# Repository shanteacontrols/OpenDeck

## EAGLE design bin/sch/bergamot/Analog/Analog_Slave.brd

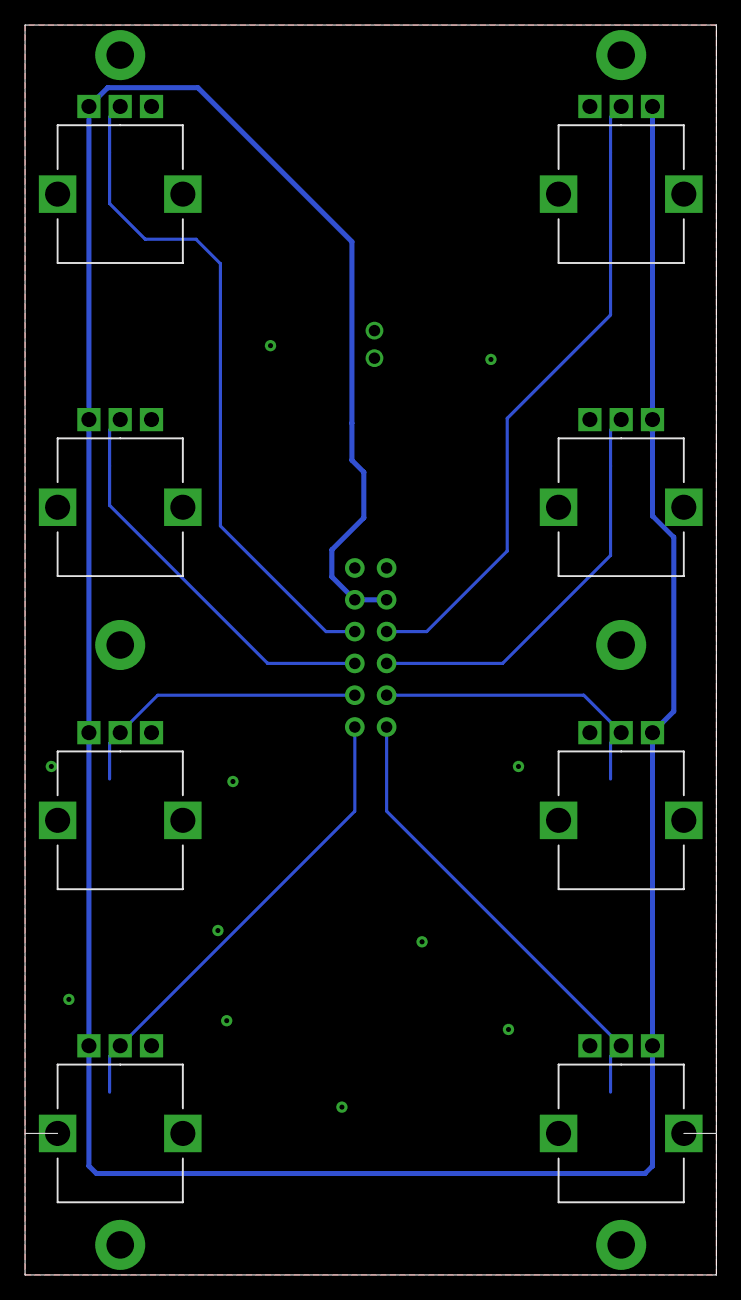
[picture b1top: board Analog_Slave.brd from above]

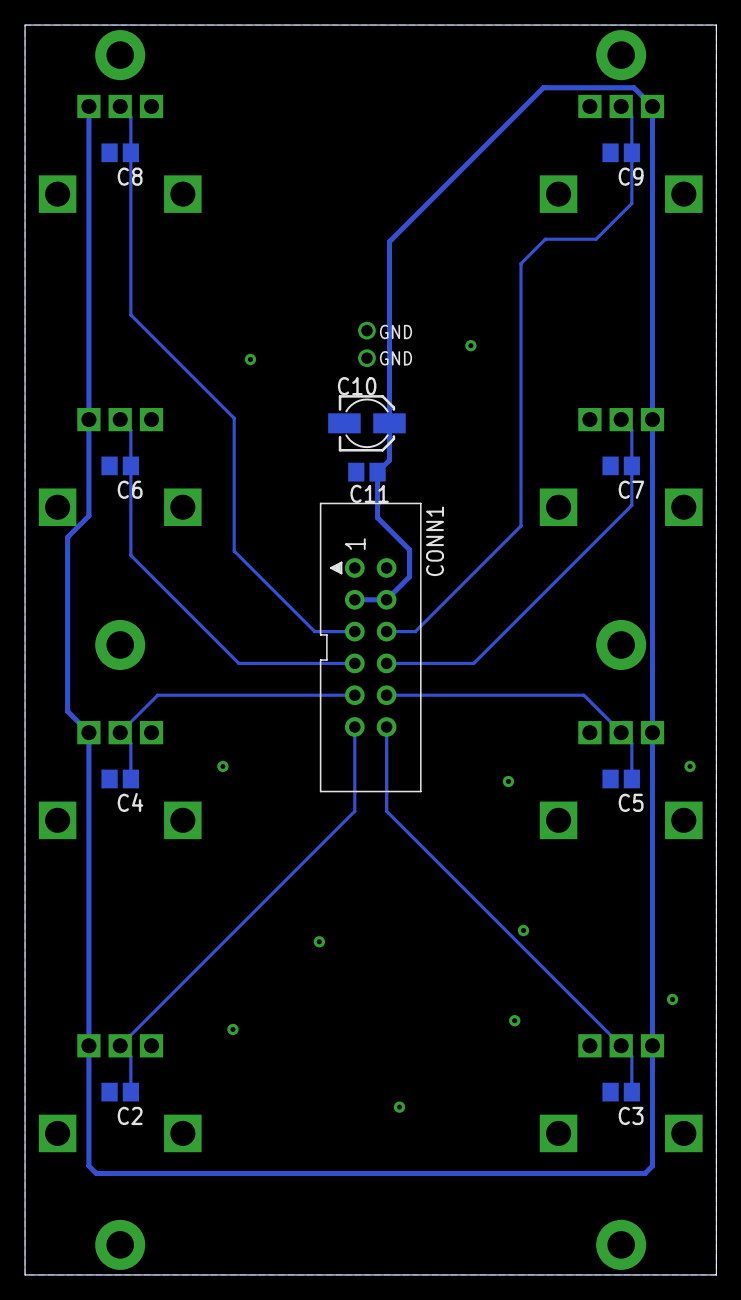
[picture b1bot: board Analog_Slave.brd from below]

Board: 2 copper layers, 55.2 x 99.8 mm, 19 parts (11 on the bottom side), 10 nets.

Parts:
C2, C3, C4, C5, C6, C7, C8, C9, C11: 100n; C0805
C10: 10u; 153CLV-0405
CONN1: PINHD-2X06-IDC-2.54-V; IDC-12P-2.54
R3, R4, R5, R6, R7, R8, R9, R10: 10k; PTV09A-4025F-B103

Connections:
+3V3: C10.+, C11.1, CONN1.3, CONN1.4, R3.1, R4.3, R5.1, R6.3, R7.1, R8.3, R9.1, R10.3
AS_1: C2.1, CONN1.11, R3.2
AS_2: C3.1, CONN1.12, R4.2
AS_3: C4.1, CONN1.9, R5.2
AS_4: C5.1, CONN1.10, R6.2
AS_5: C6.1, CONN1.7, R7.2
AS_6: C7.1, CONN1.8, R8.2
AS_7: C8.1, CONN1.5, R9.2
AS_8: C9.1, CONN1.6, R10.2
GND: C2.2, C3.2, C4.2, C5.2, C6.2, C7.2, C8.2, C9.2, C10.-, C11.2, CONN1.1, CONN1.2, R3.3, R3.S1, R3.S2, R4.1, R4.S1, R4.S2, R5.3, R5.S1, R5.S2, R6.1, R6.S1, R6.S2, R7.3, R7.S1, R7.S2, R8.1, R8.S1, R8.S2, R9.3, R9.S1, R9.S2, R10.1, R10.S1, R10.S2

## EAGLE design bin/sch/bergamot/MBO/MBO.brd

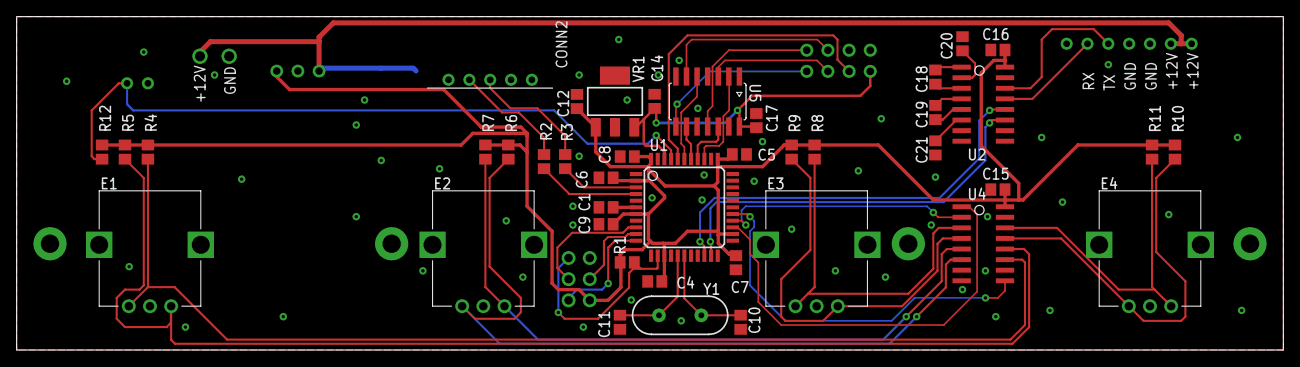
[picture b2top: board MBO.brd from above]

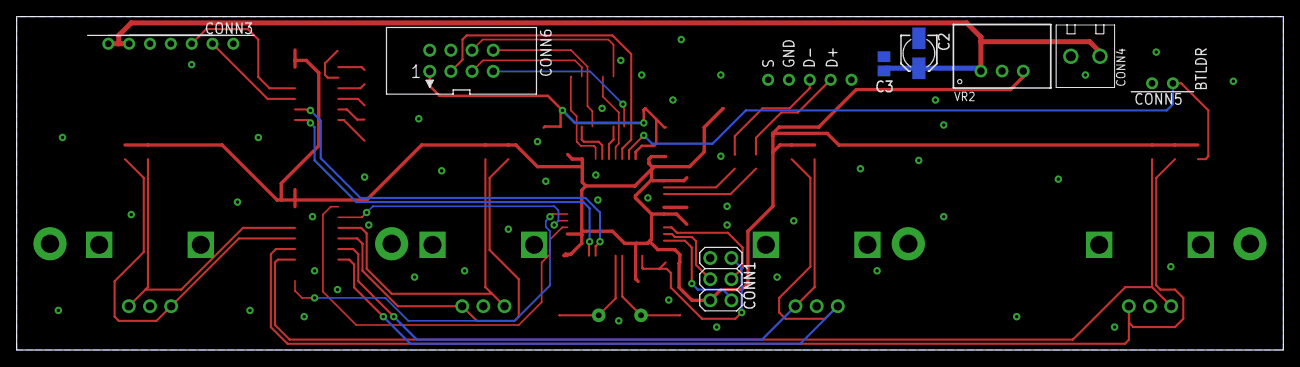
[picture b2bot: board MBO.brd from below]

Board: 2 copper layers, 152.0 x 40.0 mm, 49 parts (8 on the bottom side), 46 nets.

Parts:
C1: 1u; C0805
C2: 10n; 153CLV-0405
C3, C4, C5, C6, C7, C8, C9, C15, C16, C17, C18, C19, C20, C21: 100n; C0805
C10, C11: 22p; C0805
C12, C14: 4.7u; C0805
CONN1: PINHD-2X03-TH-2.54MM-V; 2X03-2.54-V
CONN2: PINHD-1X05-JST-XH-H; JST-XH-05P-H
CONN3: PINHD-1X07-JST-H; JST-XH-07P-H
CONN4: PINHD-1X02-MOLEX-39357-0002; MOLEX-39357-0002
CONN5: PINHD-1X02-JST-XH-H; JST-XH-02P-H
CONN6: PINHD-2X04-IDC-2.54-V; IDC-08P-2.54
E1, E2, E3, E4: ALPS-EC12E24404AX; EC12E-1
R1, R4, R5, R6, R7, R8, R9, R10, R11, R12: 10k; R0805
R2, R3: 22; R0805
U1: ATMEGA-32U4TQFP; TQFP-44
U2: MAX3232; SO16
U4: 74HC165; SO16
U5: 74AHC125; SOIC14
VR1: MCP1825; SOT223
VR2: TSR-1-2450
Y1: 16MHz; HC49US

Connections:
+3V3: C14.1, C17.1, CONN6.1, U1.42, U5.14, VR1.3
+5V: C4.1, C5.1, C6.1, C7.1, C8.1, C9.1, C12.1, C15.2, C16.2, CONN1.2, R1.2, R4.2, R5.2, R6.2, R7.2, R8.2, R9.2, R10.2, R11.2, R12.2, U1.2, U1.7, U1.14, U1.24, U1.34, U1.44, U2.16, U4.16, VR1.1, VR2.3
+12V: C2.+, C3.1, CONN3.6, CONN3.7, CONN4.P$1, VR2.1
BTLDR_BUTTON: CONN5.2, R12.1, U1.41
C1+: C18.1, U2.1
C1-: C18.2, U2.3
C2+: C19.1, U2.4
C2-: C19.2, U2.5
D+: R2.1, U1.4
D+R: CONN2.2, R2.2
D-: R3.1, U1.3
D-R: CONN2.3, R3.2
DISPLAY_RX_5V: U1.20, U2.12
DISPLAY_RX_RS: CONN3.2, U2.13
DISPLAY_TX_5V: U1.21, U2.11
DISPLAY_TX_RS: CONN3.3, U2.14
E1A: E1.A, R4.1, U4.11
E1B: E1.B, R5.1, U4.12
E2A: E2.A, R6.1, U4.6
E2B: E2.B, R7.1, U4.5
E3A: E3.A, R8.1, U4.3
E3B: E3.B, R9.1, U4.4
E4A: E4.A, R10.1, U4.13
E4B: E4.B, R11.1, U4.14
GND: C1.2, C2.-, C3.2, C4.2, C5.2, C6.2, C7.2, C8.2, C9.2, C10.1, C11.1, C12.2, C14.2, C15.1, C16.1, C17.2, C20.2, C21.2, CONN1.6, CONN2.4, CONN2.5, CONN3.4, CONN3.5, CONN4.P$2, CONN5.1, CONN6.2, CONN6.4, E1.C, E1.S1, E1.S2, E2.C, E2.S1, E2.S2, E3.C, E3.S1, E3.S2, E4.C, E4.S1, E4.S2, U1.5, U1.15, U1.23, U1.35, U1.43, U2.10, U2.15, U4.8, U4.15, U5.1, U5.4, U5.7, U5.10, U5.13, VR1.2, VR1.4, VR2.2
MISO: CONN1.1, U1.11
MOSI: CONN1.4, U1.10
MUX_COMMON_1: CONN6.3, U1.40
MUX_S0_3V3: CONN6.8, U5.11
MUX_S0_5V: U1.37, U5.12
MUX_S1_3V3: CONN6.7, U5.8
MUX_S1_5V: U1.38, U5.9
MUX_S2_3V3: CONN6.5, U5.3
MUX_S2_5V: U1.36, U5.2
MUX_S3_3V3: CONN6.6, U5.6
MUX_S3_5V: U1.39, U5.5
unnamed: C1.1, U1.6
RESET: CONN1.5, R1.1, U1.13
SCK: CONN1.3, U1.9
SR_DIN_CLOCK: U1.26, U4.2
SR_DIN_DATA: U1.27, U4.9
SR_DIN_LATCH: U1.25, U4.1
V+: C20.1, U2.2
V-: C21.1, U2.6
XTAL1: C10.2, U1.17, Y1.1
XTAL2: C11.2, U1.16, Y1.2

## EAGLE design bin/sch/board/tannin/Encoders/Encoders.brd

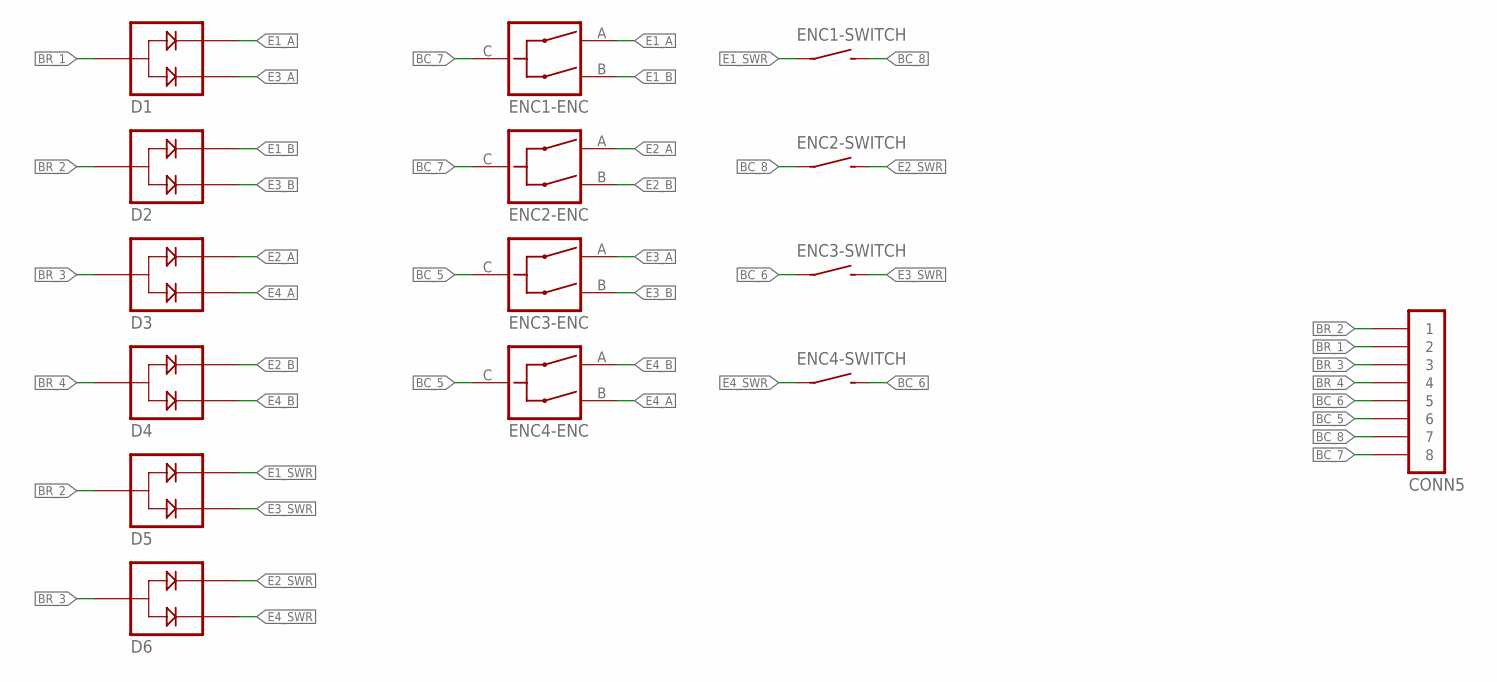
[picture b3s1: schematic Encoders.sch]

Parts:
CONN5: PINHD-1X08-FFC-1MM; MOLEX-52793-0870
D1, D2, D3, D4, D5, D6: BAW56; SOT23
ENC1, ENC2, ENC3, ENC4: BOURNS-PEC12R-4XXXF-SXXXX; PEC12R-42XXF-S0024

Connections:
BC_5: CONN5.6, ENC3.C, ENC4.C
BC_6: CONN5.5, ENC3.SW1 (1), ENC4.SW2 (2)
BC_7: CONN5.8, ENC1.C, ENC2.C
BC_8: CONN5.7, ENC1.SW2 (2), ENC2.SW1 (1)
BR_1: CONN5.2, D1.3
BR_2: CONN5.1, D2.3, D5.3
BR_3: CONN5.3, D3.3, D6.3
BR_4: CONN5.4, D4.3
E1_A: D1.2, ENC1.A
E1_B: D2.2, ENC1.B
E1_SWR: D5.2, ENC1.SW1 (1)
E2_A: D3.2, ENC2.A
E2_B: D4.2, ENC2.B
E2_SWR: D6.2, ENC2.SW2 (2)
E3_A: D1.1, ENC3.A
E3_B: D2.1, ENC3.B
E3_SWR: D5.1, ENC3.SW2 (2)
E4_A: D3.1, ENC4.B
E4_B: D4.1, ENC4.A
E4_SWR: D6.1, ENC4.SW1 (1)

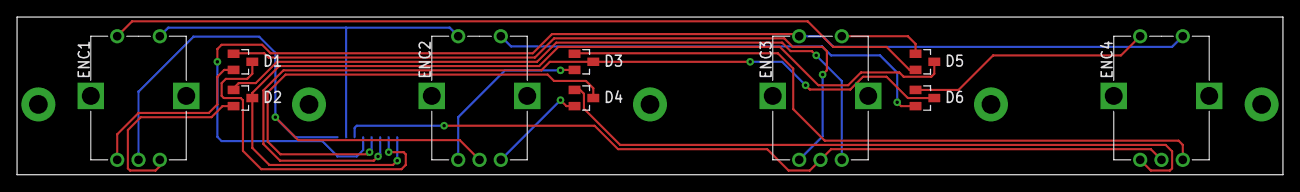
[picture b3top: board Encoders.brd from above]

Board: 2 copper layers, 148.5 x 18.5 mm, 11 parts (1 on the bottom side), 20 nets.

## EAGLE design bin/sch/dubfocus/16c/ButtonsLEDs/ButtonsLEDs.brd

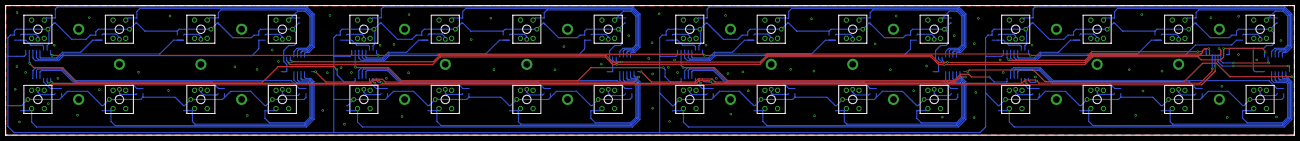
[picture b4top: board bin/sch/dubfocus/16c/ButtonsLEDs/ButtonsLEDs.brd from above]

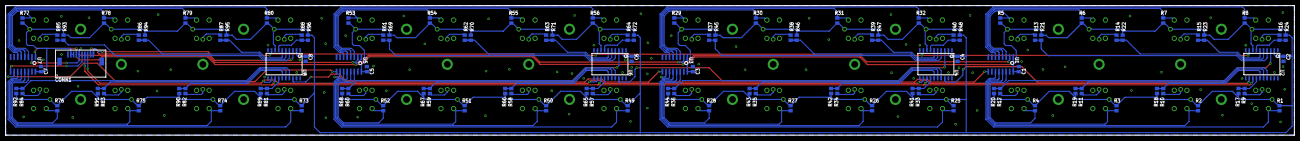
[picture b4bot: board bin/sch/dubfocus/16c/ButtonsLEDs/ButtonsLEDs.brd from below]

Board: 2 copper layers, 458.7 x 46.1 mm, 145 parts (113 on the bottom side), 111 nets.

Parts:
C1, C2, C3, C4, C5, C6, C7, C8: 100n; C0805
CONN1: PINHD-1X10-FFC-1MM-Z; MOLEX-52271-1079
R1, R2, R3, R4, R5, R6, R7, R8, R17, R18, R19, R20, R21, R22, R23, R24, R25, R26, R27, R28, R29, R30, R31, R32, R41, R42, R43, R44, R45, R46, R47, R48, R49, R50, R51, R52, R53, R54, R55, R56, R65, R66, R67, R68, R69, R70, R71, R72, R73, R74, R75, R76, R77, R78, R79, R80, R89, R90, R91, R92, R93, R94, R95, R96: 4k7; R0805
R9, R10, R11, R12, R13, R14, R15, R16, R33, R34, R35, R36, R37, R38, R39, R40, R57, R58, R59, R60, R61, R62, R63, R64, R81, R82, R83, R84, R85, R86, R87, R88: 750; R0805
SW1, SW2, SW3, SW4, SW5, SW6, SW7, SW8, SW9, SW10, SW11, SW12, SW13, SW14, SW15, SW16, SW17, SW18, SW19, SW20, SW21, SW22, SW23, SW24, SW25, SW26, SW27, SW28, SW29, SW30, SW31, SW32: OMRON-B3W-9
U1, U3, U5, U7: 74HC165; SO16
U2, U4, U6, U8: TPIC6B595; SOIC20

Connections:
+3V3: C1.1, C2.1, C3.1, C4.1, C5.1, C6.1, C7.1, C8.1, CONN1.2, CONN1.3, R1.2, R2.2, R3.2, R4.2, R5.2, R6.2, R7.2, R8.2, R17.2, R18.2, R19.2, R20.2, R21.2, R22.2, R23.2, R24.2, R25.2, R26.2, R27.2, R28.2, R29.2, R30.2, R31.2, R32.2, R41.2, R42.2, R43.2, R44.2, R45.2, R46.2, R47.2, R48.2, R49.2, R50.2, R51.2, R52.2, R53.2, R54.2, R55.2, R56.2, R65.2, R66.2, R67.2, R68.2, R69.2, R70.2, R71.2, R72.2, R73.2, R74.2, R75.2, R76.2, R77.2, R78.2, R79.2, R80.2, R89.2, R90.2, R91.2, R92.2, R93.2, R94.2, R95.2, R96.2, SW1.6-A, SW2.6-A, SW3.6-A, SW4.6-A, SW5.6-A, SW6.6-A, SW7.6-A, SW8.6-A, SW9.6-A, SW10.6-A, SW11.6-A, SW12.6-A, SW13.6-A, SW14.6-A, SW15.6-A, SW16.6-A, SW17.6-A, SW18.6-A, SW19.6-A, SW20.6-A, SW21.6-A, SW22.6-A, SW23.6-A, SW24.6-A, SW25.6-A, SW26.6-A, SW27.6-A, SW28.6-A, SW29.6-A, SW30.6-A, SW31.6-A, SW32.6-A, U1.16, U2.2, U2.8, U3.16, U4.2, U4.8, U5.16, U6.2, U6.8, U7.16, U8.2, U8.8
BUTTON1: R1.1, SW1.1, U1.11
BUTTON2: R2.1, SW2.1, U1.12
BUTTON3: R3.1, SW3.1, U1.13
BUTTON4: R4.1, SW4.1, U1.14
BUTTON5: R5.1, SW5.1, U1.3
BUTTON6: R6.1, SW6.1, U1.4
BUTTON7: R7.1, SW7.1, U1.5
BUTTON8: R8.1, SW8.1, U1.6
BUTTON9: R25.1, SW9.1, U3.11
BUTTON10: R26.1, SW10.1, U3.12
BUTTON11: R27.1, SW11.1, U3.13
BUTTON12: R28.1, SW12.1, U3.14
BUTTON13: R29.1, SW13.1, U3.3
BUTTON14: R30.1, SW14.1, U3.4
BUTTON15: R31.1, SW15.1, U3.5
BUTTON16: R32.1, SW16.1, U3.6
BUTTON17: R49.1, SW17.1, U5.11
BUTTON18: R50.1, SW18.1, U5.12
BUTTON19: R51.1, SW19.1, U5.13
BUTTON20: R52.1, SW20.1, U5.14
BUTTON21: R53.1, SW21.1, U5.3
BUTTON22: R54.1, SW22.1, U5.4
BUTTON23: R55.1, SW23.1, U5.5
BUTTON24: R56.1, SW24.1, U5.6
BUTTON25: R73.1, SW25.1, U7.11
BUTTON26: R74.1, SW26.1, U7.12
BUTTON27: R75.1, SW27.1, U7.13
BUTTON28: R76.1, SW28.1, U7.14
BUTTON29: R77.1, SW29.1, U7.3
BUTTON30: R78.1, SW30.1, U7.4
BUTTON31: R79.1, SW31.1, U7.5
BUTTON32: R80.1, SW32.1, U7.6
GND: C1.2, C2.2, C3.2, C4.2, C5.2, C6.2, C7.2, C8.2, CONN1.1, SW1.3, SW2.3, SW3.3, SW4.3, SW5.3, SW6.3, SW7.3, SW8.3, SW9.3, SW10.3, SW11.3, SW12.3, SW13.3, SW14.3, SW15.3, SW16.3, SW17.3, SW18.3, SW19.3, SW20.3, SW21.3, SW22.3, SW23.3, SW24.3, SW25.3, SW26.3, SW27.3, SW28.3, SW29.3, SW30.3, SW31.3, SW32.3, U1.8, U1.15, U2.10, U2.11, U2.19, U3.8, U3.15, U4.10, U4.11, U4.19, U5.8, U5.15, U6.10, U6.11, U6.19, U7.8, U7.15, U8.10, U8.11, U8.19
LED1: R9.2, R17.1, U2.14
LED1_R: R9.1, SW1.6-C
LED2: R10.2, R18.1, U2.15
LED2_R: R10.1, SW2.6-C
LED3: R11.2, R19.1, U2.16
LED3_R: R11.1, SW3.6-C
LED4: R12.2, R20.1, U2.17
LED4_R: R12.1, SW4.6-C
LED5: R13.2, R21.1, U2.4
LED5_R: R13.1, SW5.6-C
LED6: R14.2, R22.1, U2.5
LED6_R: R14.1, SW6.6-C
LED7: R15.2, R23.1, U2.6
LED7_R: R15.1, SW7.6-C
LED8: R16.2, R24.1, U2.7
LED8_R: R16.1, SW8.6-C
LED9: R33.2, R41.1, U4.14
LED9_R: R33.1, SW9.6-C
LED10: R34.2, R42.1, U4.15
LED10_R: R34.1, SW10.6-C
LED11: R35.2, R43.1, U4.16
LED11_R: R35.1, SW11.6-C
LED12: R36.2, R44.1, U4.17
LED12_R: R36.1, SW12.6-C
LED13: R37.2, R45.1, U4.4
LED13_R: R37.1, SW13.6-C
LED14: R38.2, R46.1, U4.5
LED14_R: R38.1, SW14.6-C
LED15: R39.2, R47.1, U4.6
LED15_R: R39.1, SW15.6-C
LED16: R40.2, R48.1, U4.7
LED16_R: R40.1, SW16.6-C
LED17: R57.2, R65.1, U6.14
LED17_R: R57.1, SW17.6-C
LED18: R58.2, R66.1, U6.15
LED18_R: R58.1, SW18.6-C
LED19: R59.2, R67.1, U6.16
LED19_R: R59.1, SW19.6-C
LED20: R60.2, R68.1, U6.17
LED20_R: R60.1, SW20.6-C
LED21: R61.2, R69.1, U6.4
LED21_R: R61.1, SW21.6-C
LED22: R62.2, R70.1, U6.5
LED22_R: R62.1, SW22.6-C
LED23: R63.2, R71.1, U6.6
LED23_R: R63.1, SW23.6-C
LED24: R64.2, R72.1, U6.7
LED24_R: R64.1, SW24.6-C
LED25: R81.2, R89.1, U8.14
LED25_R: R81.1, SW25.6-C
LED26: R82.2, R90.1, U8.15
LED26_R: R82.1, SW26.6-C
LED27: R83.2, R91.1, U8.16
LED27_R: R83.1, SW27.6-C
LED28: R84.2, R92.1, U8.17
LED28_R: R84.1, SW28.6-C
LED29: R85.2, R93.1, U8.4
LED29_R: R85.1, SW29.6-C
LED30: R86.2, R94.1, U8.5
LED30_R: R86.1, SW30.6-C
LED31: R87.2, R95.1, U8.6
LED31_R: R87.1, SW31.6-C
LED32: R88.2, R96.1, U8.7
LED32_R: R88.1, SW32.6-C
SR_IN_CLOCK: CONN1.5, U1.2, U3.2, U5.2, U7.2
SR_IN_DAISY_OUT_1: U5.9, U7.10
SR_IN_DAISY_OUT_2: U3.9, U5.10
SR_IN_DAISY_OUT_3: U1.9, U3.10
SR_IN_DATA: CONN1.6, U7.9
SR_IN_LATCH: CONN1.4, U1.1, U3.1, U5.1, U7.1
SR_OUT_CLOCK: CONN1.7, U2.13, U4.13, U6.13, U8.13
SR_OUT_DAISY_OUT_1: U6.3, U8.18
SR_OUT_DAISY_OUT_2: U4.3, U6.18
SR_OUT_DAISY_OUT_3: U2.3, U4.18
SR_OUT_DATA: CONN1.9, U8.3
SR_OUT_LATCH: CONN1.8, U2.12, U4.12, U6.12, U8.12
SR_OUT_OE: CONN1.10, U2.9, U4.9, U6.9, U8.9

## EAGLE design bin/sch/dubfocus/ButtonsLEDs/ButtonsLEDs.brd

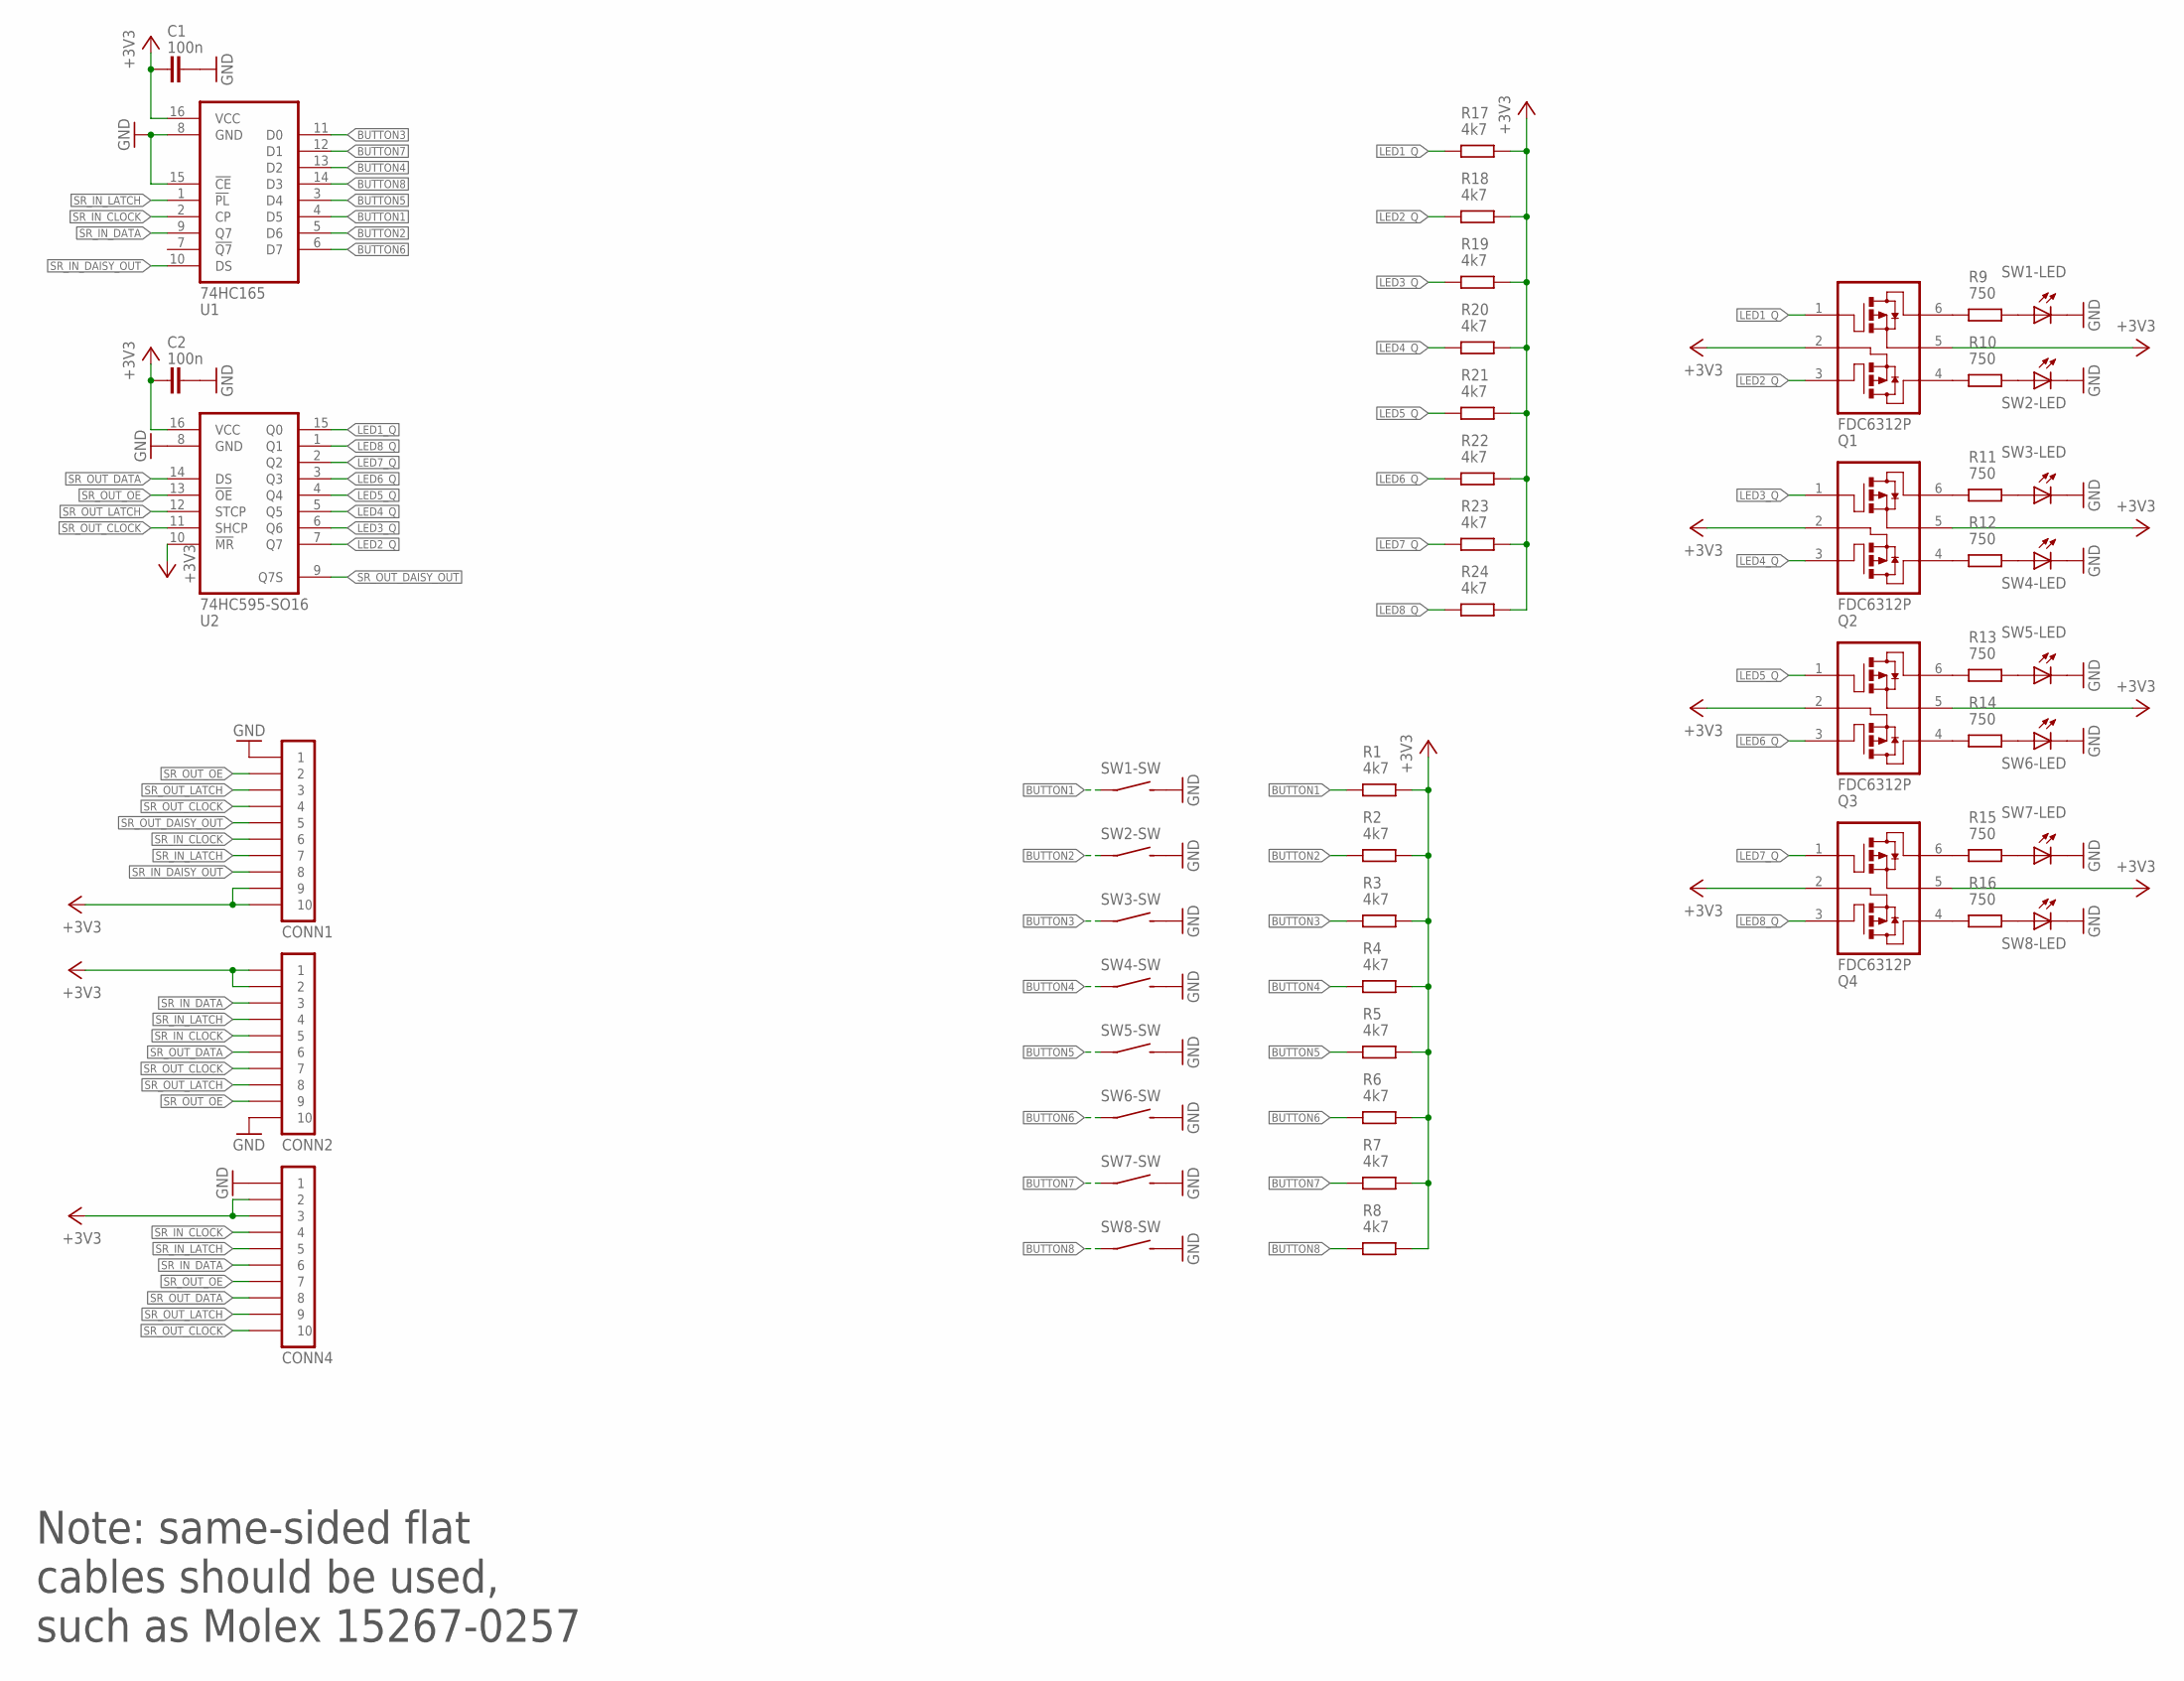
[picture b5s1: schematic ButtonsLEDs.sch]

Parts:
C1, C2: 100n; C0805
CONN1, CONN2, CONN4: PINHD-1X10-FFC-1MM-Z; MOLEX-52271-1079
Q1, Q2, Q3, Q4: FDC6312P; SSOT6
R1, R2, R3, R4, R5, R6, R7, R8, R17, R18, R19, R20, R21, R22, R23, R24: 4k7; R0805
R9, R10, R11, R12, R13, R14, R15, R16: 750; R0805
SW1, SW2, SW3, SW4, SW5, SW6, SW7, SW8: OMRON-B3W-9
U1: 74HC165; SO16
U2: 74HC595-SO16; SO16

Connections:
+3V3: C1.1, C2.1, CONN1.9, CONN1.10, CONN2.1, CONN2.2, CONN4.2, CONN4.3, Q1.2 (S2), Q1.5 (S1), Q2.2 (S2), Q2.5 (S1), Q3.2 (S2), Q3.5 (S1), Q4.2 (S2), Q4.5 (S1), R1.2, R2.2, R3.2, R4.2, R5.2, R6.2, R7.2, R8.2, R17.2, R18.2, R19.2, R20.2, R21.2, R22.2, R23.2, R24.2, U1.16 (VCC), U2.10 (!MR), U2.16 (VCC)
BUTTON1: R1.1, SW1.1, U1.4 (D5)
BUTTON2: R2.1, SW2.1, U1.5 (D6)
BUTTON3: R3.1, SW3.1, U1.11 (D0)
BUTTON4: R4.1, SW4.1, U1.13 (D2)
BUTTON5: R5.1, SW5.1, U1.3 (D4)
BUTTON6: R6.1, SW6.1, U1.6 (D7)
BUTTON7: R7.1, SW7.1, U1.12 (D1)
BUTTON8: R8.1, SW8.1, U1.14 (D3)
GND: C1.2, C2.2, CONN1.1, CONN2.10, CONN4.1, SW1.3 (2), SW1.6-C (C), SW2.3 (2), SW2.6-C (C), SW3.3 (2), SW3.6-C (C), SW4.3 (2), SW4.6-C (C), SW5.3 (2), SW5.6-C (C), SW6.3 (2), SW6.6-C (C), SW7.3 (2), SW7.6-C (C), SW8.3 (2), SW8.6-C (C), U1.8 (GND), U1.15 (!CE), U2.8 (GND)
LED1_Q: Q1.1 (G1), R17.1, U2.15 (Q0)
LED2_Q: Q1.3 (G2), R18.1, U2.7 (Q7)
LED3_Q: Q2.1 (G1), R19.1, U2.6 (Q6)
LED4_Q: Q2.3 (G2), R20.1, U2.5 (Q5)
LED5_Q: Q3.1 (G1), R21.1, U2.4 (Q4)
LED6_Q: Q3.3 (G2), R22.1, U2.3 (Q3)
LED7_Q: Q4.1 (G1), R23.1, U2.2 (Q2)
LED8_Q: Q4.3 (G2), R24.1, U2.1 (Q1)
unnamed: R9.2, SW1.6-A (A)
unnamed: R10.2, SW2.6-A (A)
unnamed: R11.2, SW3.6-A (A)
unnamed: R12.2, SW4.6-A (A)
unnamed: R13.2, SW5.6-A (A)
unnamed: R15.2, SW7.6-A (A)
unnamed: R16.2, SW8.6-A (A)
unnamed: R14.2, SW6.6-A (A)
unnamed: Q1.6 (D1), R9.1
unnamed: Q1.4 (D2), R10.1
unnamed: Q2.6 (D1), R11.1
unnamed: Q2.4 (D2), R12.1
unnamed: Q3.6 (D1), R13.1
unnamed: Q3.4 (D2), R14.1
unnamed: Q4.6 (D1), R15.1
unnamed: Q4.4 (D2), R16.1
SR_IN_CLOCK: CONN1.6, CONN2.5, CONN4.4, U1.2 (CP)
SR_IN_DAISY_OUT: CONN1.8, U1.10 (DS)
SR_IN_DATA: CONN2.3, CONN4.6, U1.9 (Q7)
SR_IN_LATCH: CONN1.7, CONN2.4, CONN4.5, U1.1 (!PL)
SR_OUT_CLOCK: CONN1.4, CONN2.7, CONN4.10, U2.11 (SHCP)
SR_OUT_DAISY_OUT: CONN1.5, U2.9 (Q7S)
SR_OUT_DATA: CONN2.6, CONN4.8, U2.14 (DS)
SR_OUT_LATCH: CONN1.3, CONN2.8, CONN4.9, U2.12 (STCP)
SR_OUT_OE: CONN1.2, CONN2.9, CONN4.7, U2.13 (!OE)

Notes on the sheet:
Note: same-sided flat cables should be used, such as Molex 15267-0257

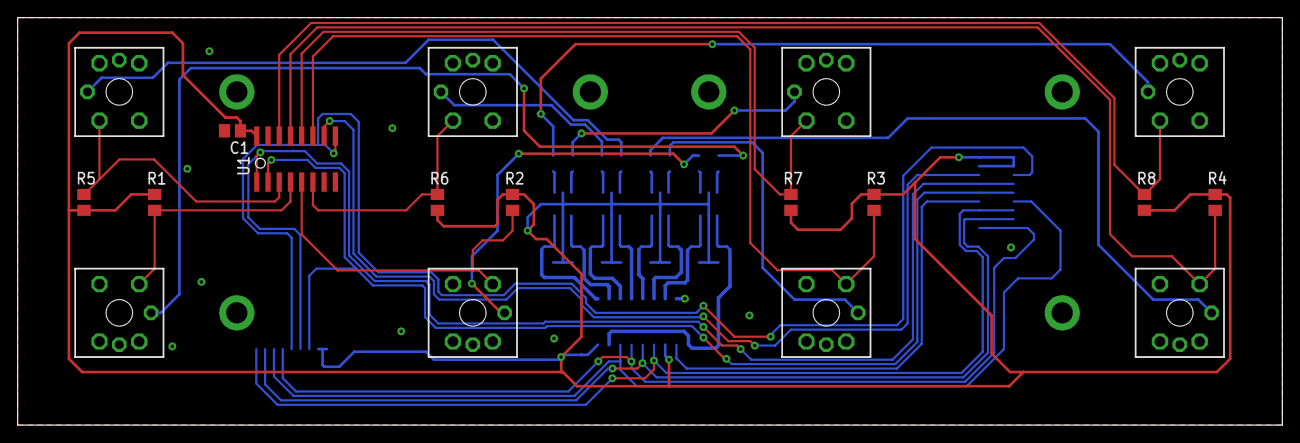
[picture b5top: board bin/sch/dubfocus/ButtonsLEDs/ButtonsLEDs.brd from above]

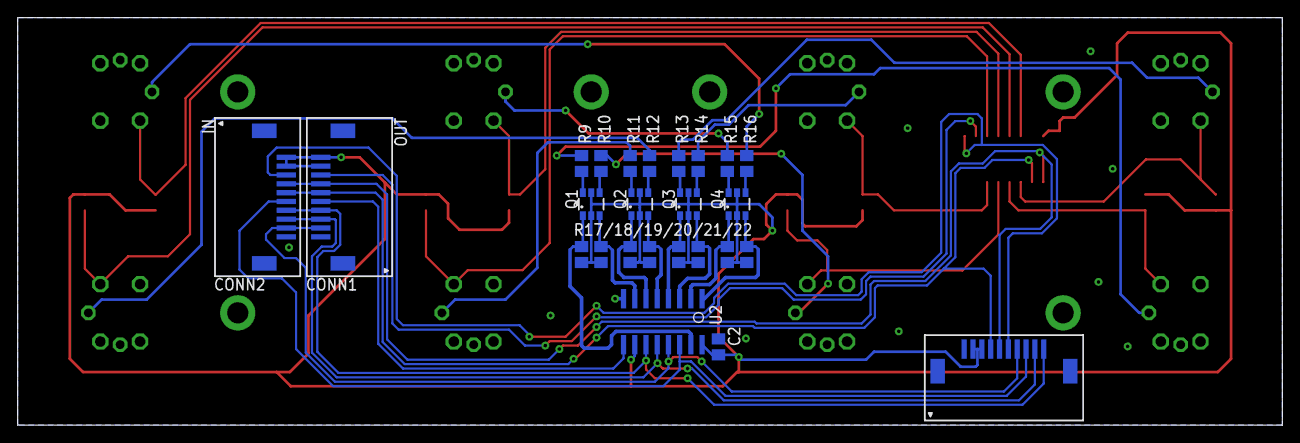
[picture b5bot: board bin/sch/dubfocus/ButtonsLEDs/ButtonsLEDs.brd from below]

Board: 2 copper layers, 143.1 x 46.1 mm, 43 parts (25 on the bottom side), 43 nets.
